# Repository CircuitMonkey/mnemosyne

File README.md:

# mnemosyne
Flash based NES Cartridge and programmer. Experimental project.

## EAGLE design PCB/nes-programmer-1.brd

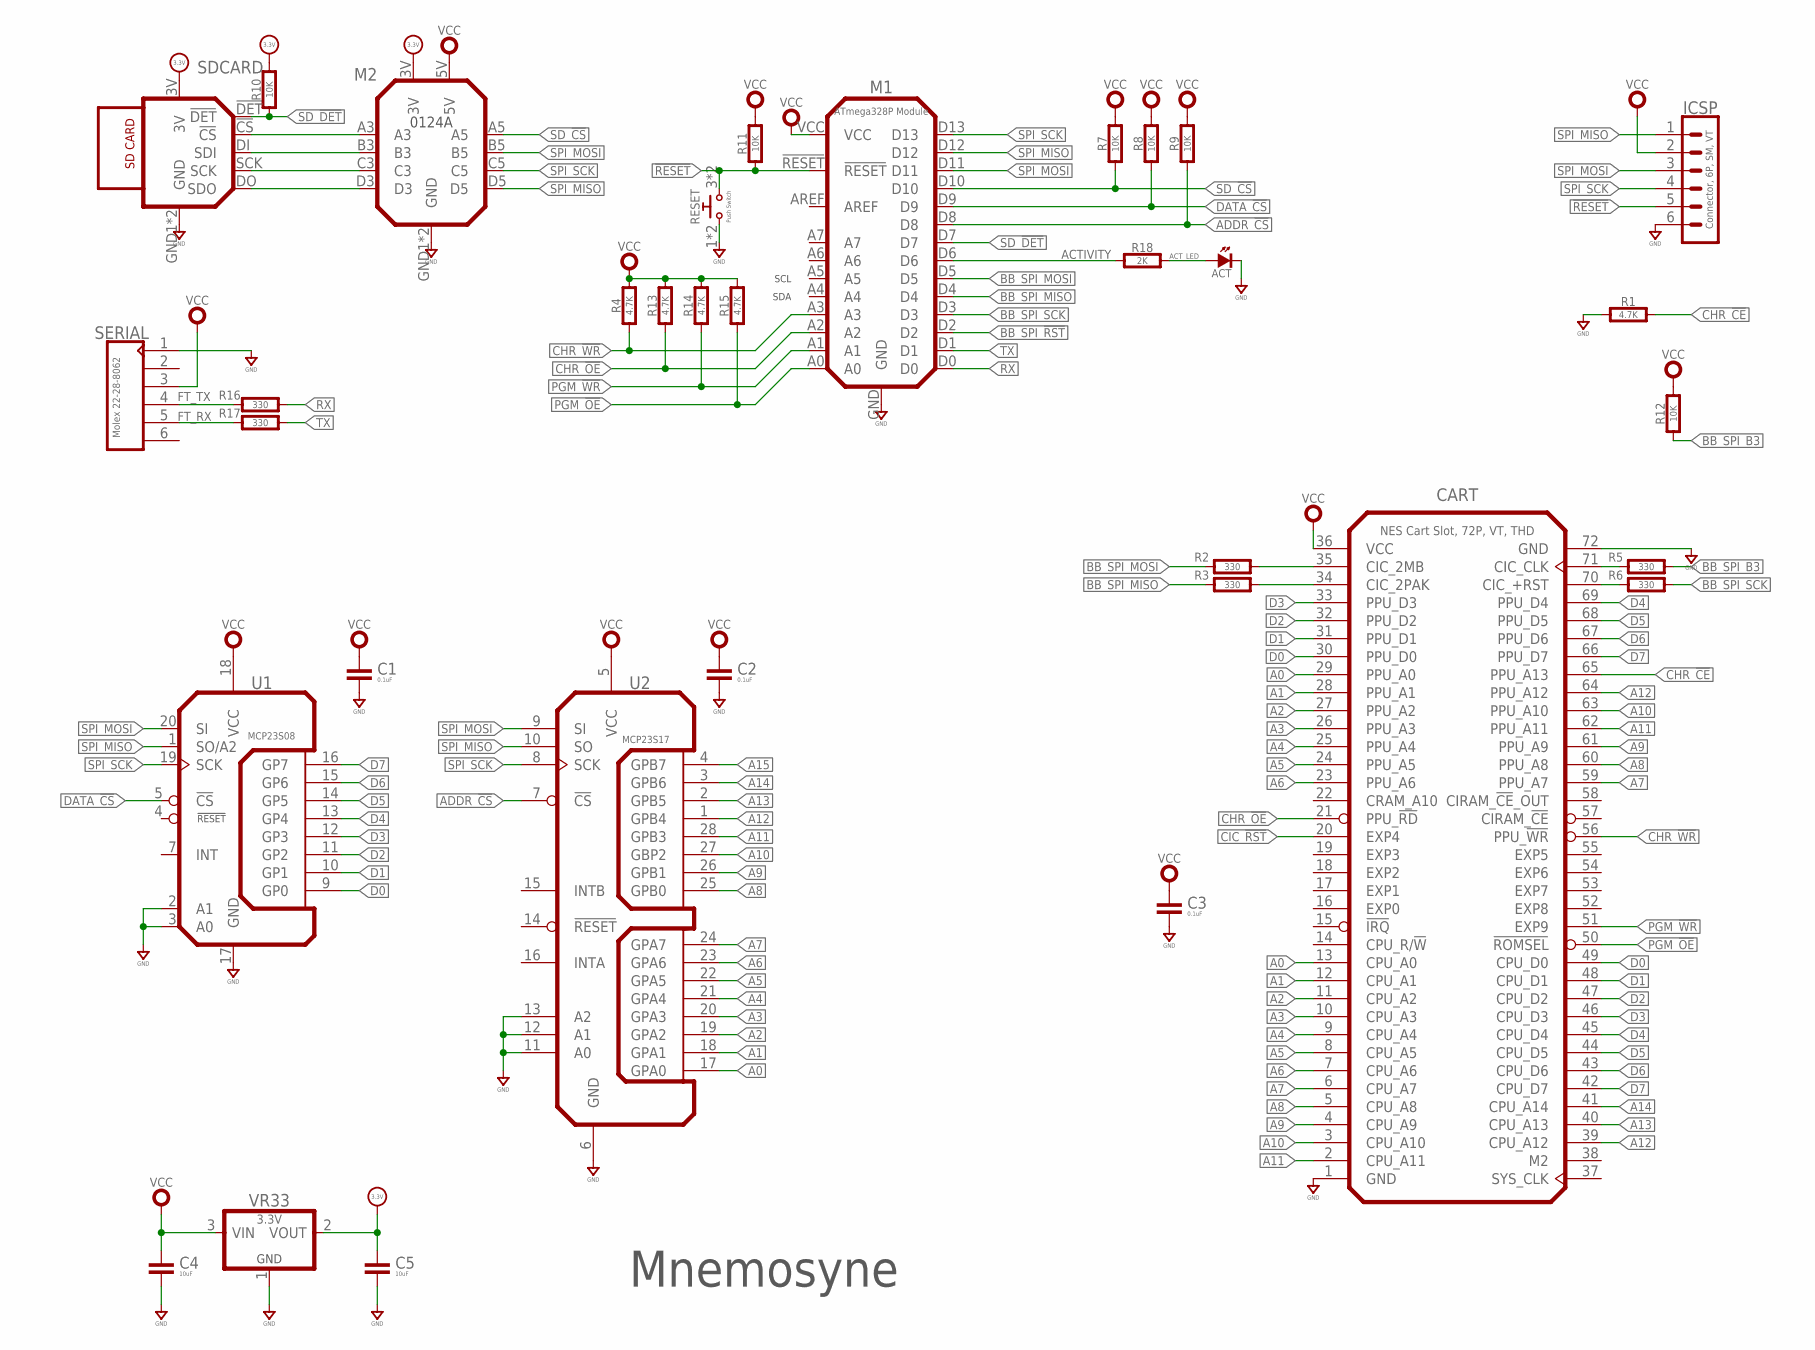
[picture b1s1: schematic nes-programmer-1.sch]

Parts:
ACT: SMT0603; SMD_0603
C1, C2, C3: 0.1uF; 0603-CAP
C4, C5: 10uF; 0603-CAP
CART: NES Cart Slot, 72P, VT, THD; NES-CONNECTOR-VT-THD
ICSP: Connector, 6P, SM, VT; BM06B-SRSS-TB
M1: ATmega328P Module; 0119A
M2: 0124A
R1, R4, R13, R14, R15: 4.7K; 0603-RES
R2, R3, R5, R6, R16, R17: 330; 0603-RES
R7, R8, R9, R10, R11, R12: 10K; 0603-RES
R18: 2K; 0603-RES
RESET: Push Switch; B3SN
SDCARD: 0127REV-A; 0127A
SERIAL: Molex 22-28-8062; MA06X1-RA-THD
U1: MCP23S08; QFN-20
U2: MCP23S17; QFN-28-6X6
VR33: 3.3V; SOT-23

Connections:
!RESET: ICSP.5, M1.!RESET, R11.1, RESET.3 (2), RESET.4 (2)
+3.3V: C5.1, M2.3V, R10.2, SDCARD.3V, VR33.2 (VOUT)
A0: CART.13 (CPU_A0), CART.29 (PPU_A0), U2.17 (GPA0)
A1: CART.12 (CPU_A1), CART.28 (PPU_A1), U2.18 (GPA1)
A2: CART.11 (CPU_A2), CART.27 (PPU_A2), U2.19 (GPA2)
A3: CART.10 (CPU_A3), CART.26 (PPU_A3), U2.20 (GPA3)
A4: CART.9 (CPU_A4), CART.25 (PPU_A4), U2.21 (GPA4)
A5: CART.8 (CPU_A5), CART.24 (PPU_A5), U2.22 (GPA5)
A6: CART.7 (CPU_A6), CART.23 (PPU_A6), U2.23 (GPA6)
A7: CART.6 (CPU_A7), CART.59 (PPU_A7), U2.24 (GPA7)
A8: CART.5 (CPU_A8), CART.60 (PPU_A8), U2.25 (GPB0)
A9: CART.4 (CPU_A9), CART.61 (PPU_A9), U2.26 (GPB1)
A10: CART.3 (CPU_A10), CART.63 (PPU_A10), U2.27 (GBP2)
A11: CART.2 (CPU_A11), CART.62 (PPU_A11), U2.28 (GPB3)
A12: CART.39 (CPU_A12), CART.64 (PPU_A12), U2.1 (GPB4)
A13: CART.40 (CPU_A13), U2.2 (GPB5)
A14: CART.41 (CPU_A14), U2.3 (GPB6)
A15: U2.4 (GPB7)
ACTIVITY: M1.D6, R18.1
ACT_LED: ACT.A, R18.2
ADDR_!CS: M1.D8, R9.1, U2.7 (!CS)
BB_SPI_!RST: M1.D2
BB_SPI_B3: R5.2, R12.1
BB_SPI_MISO: M1.D4, R3.1
BB_SPI_MOSI: M1.D5, R2.1
BB_SPI_SCK: M1.D3, R6.2
CHR_!CE: CART.65 (PPU_A13), R1.2
CHR_!OE: CART.21 (PPU_!RD), M1.A2, R13.1
CHR_!WR: CART.56 (PPU_!WR), M1.A3, R4.1
CIC_2MB: CART.35 (CIC_2MB), R2.2
CIC_2PAK: CART.34 (CIC_2PAK), R3.2
CIC_!RST: CART.20 (EXP4)
CIC_+RST: CART.70 (CIC_+RST), R6.1
CIC_CLK: CART.71 (CIC_CLK), R5.1
D0: CART.30 (PPU_D0), CART.49 (CPU_D0), U1.9 (GP0)
D1: CART.31 (PPU_D1), CART.48 (CPU_D1), U1.10 (GP1)
D2: CART.32 (PPU_D2), CART.47 (CPU_D2), U1.11 (GP2)
D3: CART.33 (PPU_D3), CART.46 (CPU_D3), U1.12 (GP3)
D4: CART.45 (CPU_D4), CART.69 (PPU_D4), U1.13 (GP4)
D5: CART.44 (CPU_D5), CART.68 (PPU_D5), U1.14 (GP5)
D6: CART.43 (CPU_D6), CART.67 (PPU_D6), U1.15 (GP6)
D7: CART.42 (CPU_D7), CART.66 (PPU_D7), U1.16 (GP7)
DATA_!CS: M1.D9, R8.1, U1.5 (!CS)
FT_RX: R17.1, SERIAL.5
FT_TX: R16.1, SERIAL.4
GND: ACT.K (C), C1.2, C2.2, C3.2, C4.2, C5.2, CART.1 (GND), CART.72 (GND), ICSP.6, M1.GND, M2.GND1 (GND), M2.GND2 (GND), R1.1, RESET.1, RESET.2 (1), SDCARD.GND1 (GND), SDCARD.GND2 (GND), SERIAL.1, U1.2 (A1), U1.3 (A0), U1.17 (GND), U2.6 (GND), U2.11 (A0), U2.12 (A1), U2.13 (A2), VR33.1 (GND)
unnamed: M2.D3, SDCARD.DO (SDO)
unnamed: M2.C3, SDCARD.SCK
unnamed: M2.B3, SDCARD.DI (SDI)
unnamed: M2.A3, SDCARD.!CS
PGM_!OE: CART.50 (!ROMSEL), M1.A0, R15.1
PGM_!WR: CART.51 (EXP9), M1.A1, R14.1
RX: M1.D0, R16.2
SD_!CS: M1.D10, M2.A5, R7.1
SD_!DET: M1.D7, R10.1, SDCARD.!DET
SPI_MISO: ICSP.1, M1.D12, M2.D5, U1.1 (SO/A2), U2.10 (SO)
SPI_MOSI: ICSP.3, M1.D11, M2.B5, U1.20 (SI), U2.9 (SI)
SPI_SCK: ICSP.4, M1.D13, M2.C5, U1.19 (SCK), U2.8 (SCK)
TX: M1.D1, R17.2
VCC: C1.1, C2.1, C3.1, C4.1, CART.36 (VCC), ICSP.2, M1.VCC, M2.5V, R4.2, R7.2, R8.2, R9.2, R11.2, R12.2, R13.2, R14.2, R15.2, SERIAL.3, U1.18 (VCC), U2.5 (VCC), VR33.3 (VIN)

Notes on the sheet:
SDA
SCL
Mnemosyne

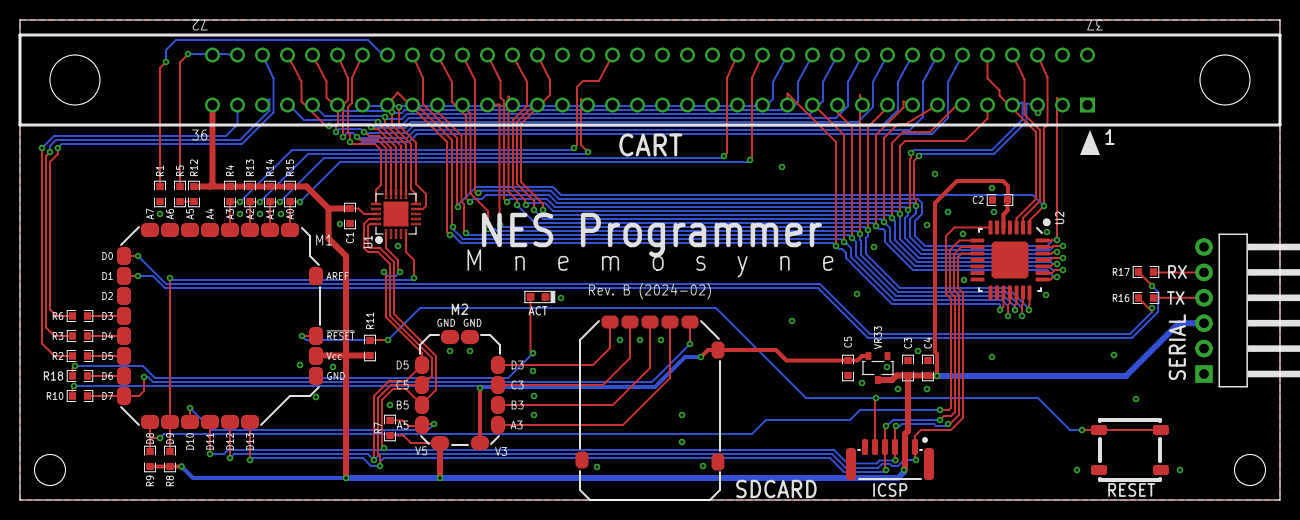
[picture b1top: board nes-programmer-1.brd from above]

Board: 2 copper layers, 126.0 x 48.0 mm, 34 parts (0 on the bottom side), 57 nets.

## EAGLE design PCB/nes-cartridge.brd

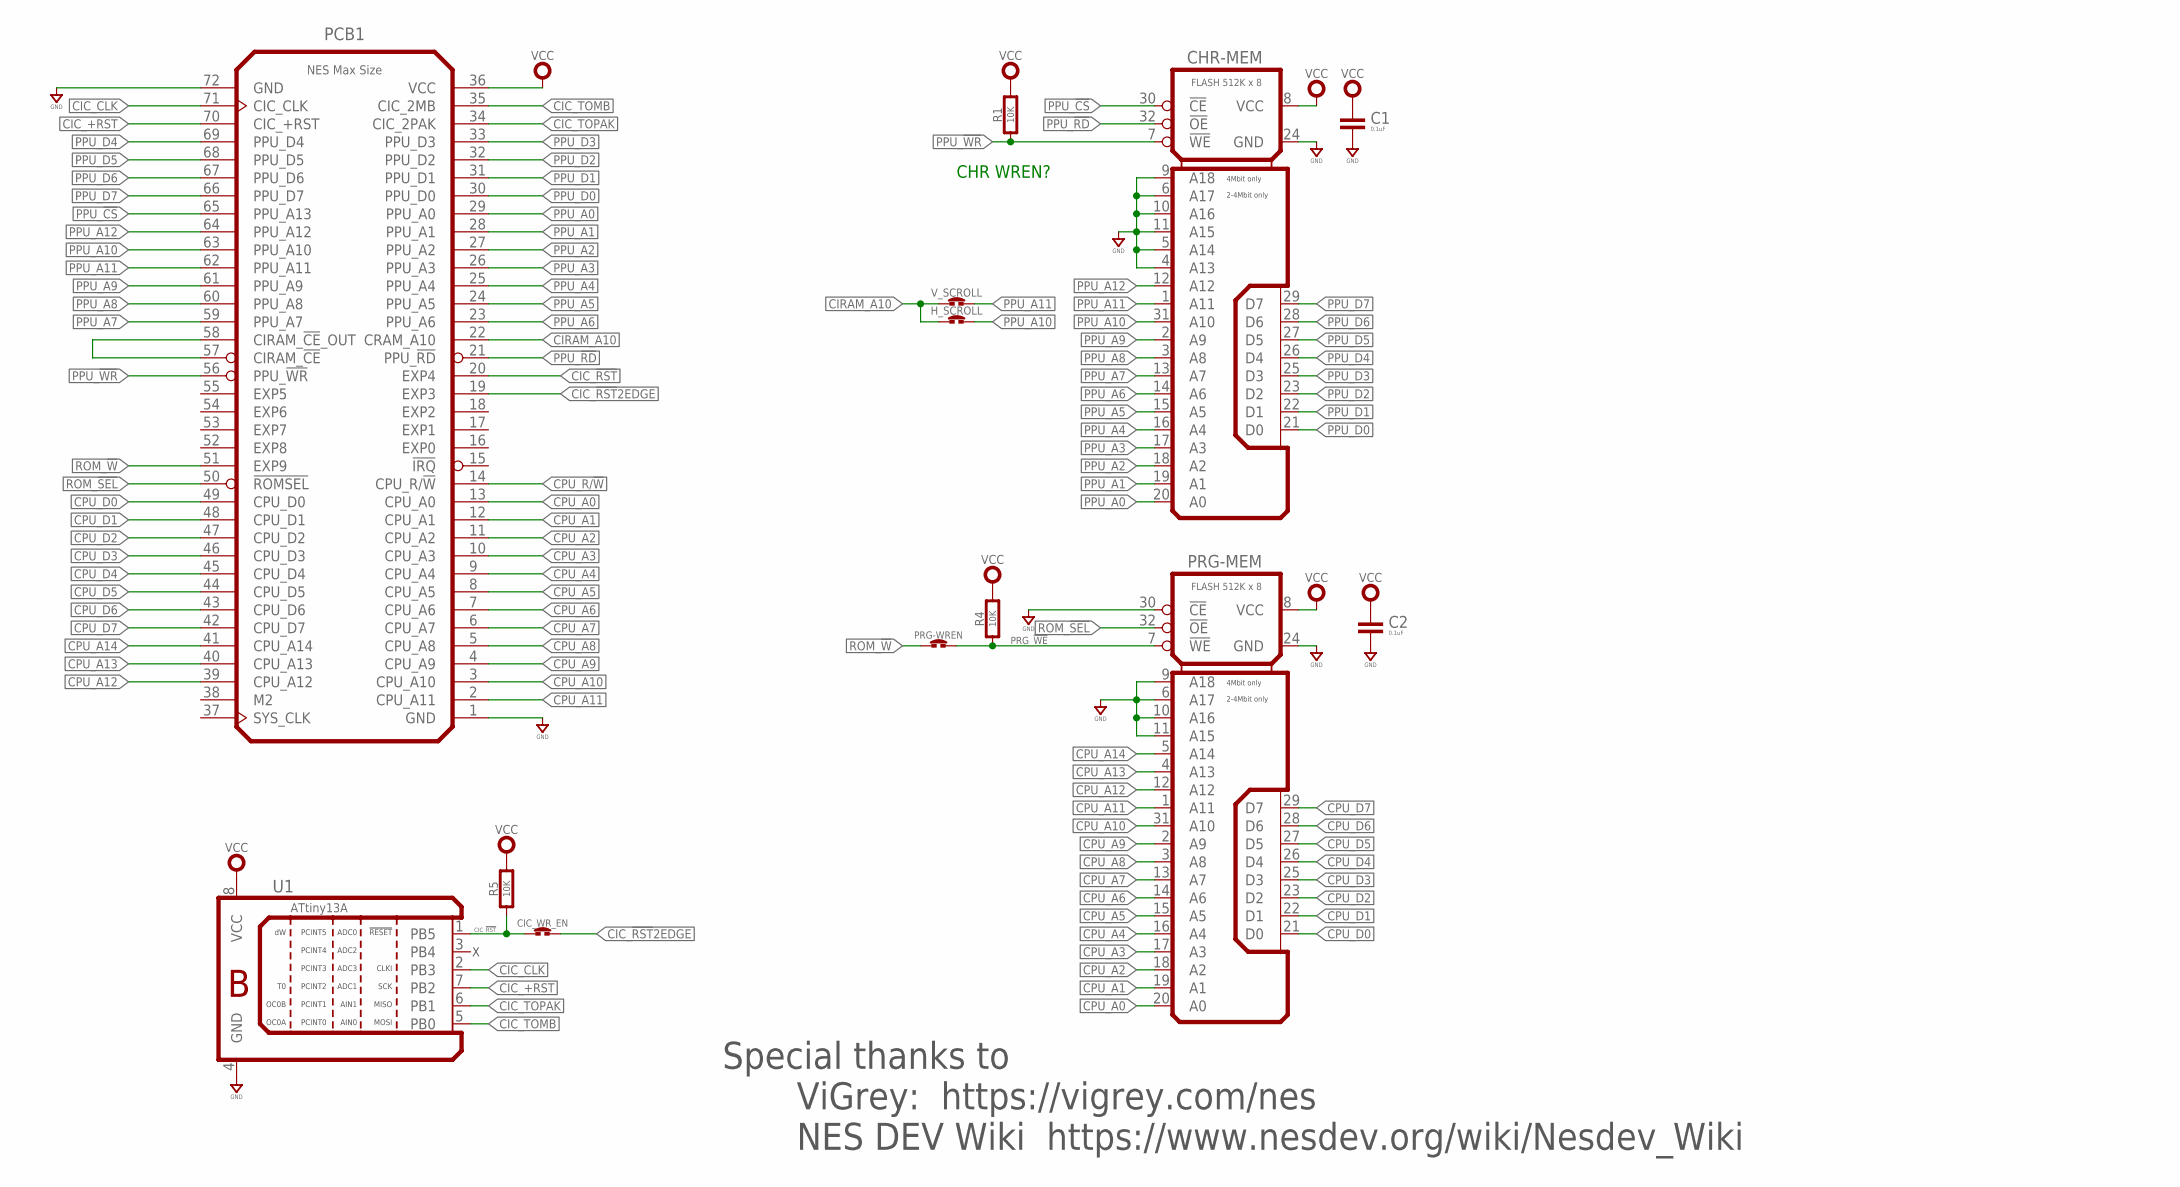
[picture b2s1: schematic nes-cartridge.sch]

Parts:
C1, C2: 0.1uF; 0603-CAP
CHR-MEM: FLASH 512K x 8; TSOP32-14X8MM
CIC_WR_EN: SOLDER_JUMPER-80MIL-RND; SOLDER_JUMP_80MIL_RND
H_SCROLL: SOLDER_JUMPER-80MIL-RND; SOLDER_JUMP_80MIL_RND
PCB1: NES Max Size; NES-1-MIN
PRG-MEM: FLASH 512K x 8; TSOP32-14X8MM
PRG-WREN: SOLDER_JUMPER-80MIL-RND; SOLDER_JUMP_80MIL_RND
R1, R4, R5: 10K; 0603-RES
U1: ATtiny13A; SOIC-8S2
V_SCROLL: SOLDER_JUMPER-80MIL-RND; SOLDER_JUMP_80MIL_RND

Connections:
CIC_!RST: CIC_WR_EN.1, PCB1.20 (EXP4), R5.1, U1.1 (PB5)
CIC_!RST!2EDGE: CIC_WR_EN.2, PCB1.19 (EXP3)
CIC_+RST: PCB1.70 (CIC_+RST), U1.7 (PB2)
CIC_CLK: PCB1.71 (CIC_CLK), U1.2 (PB3)
CIC_TOMB: PCB1.35 (CIC_2MB), U1.5 (PB0)
CIC_TOPAK: PCB1.34 (CIC_2PAK), U1.6 (PB1)
CIRAM_A10: H_SCROLL.1, PCB1.22 (CRAM_A10), V_SCROLL.1
CPU_A0: PCB1.13 (CPU_A0), PRG-MEM.20 (A0)
CPU_A1: PCB1.12 (CPU_A1), PRG-MEM.19 (A1)
CPU_A2: PCB1.11 (CPU_A2), PRG-MEM.18 (A2)
CPU_A3: PCB1.10 (CPU_A3), PRG-MEM.17 (A3)
CPU_A4: PCB1.9 (CPU_A4), PRG-MEM.16 (A4)
CPU_A5: PCB1.8 (CPU_A5), PRG-MEM.15 (A5)
CPU_A6: PCB1.7 (CPU_A6), PRG-MEM.14 (A6)
CPU_A7: PCB1.6 (CPU_A7), PRG-MEM.13 (A7)
CPU_A8: PCB1.5 (CPU_A8), PRG-MEM.3 (A8)
CPU_A9: PCB1.4 (CPU_A9), PRG-MEM.2 (A9)
CPU_A10: PCB1.3 (CPU_A10), PRG-MEM.31 (A10)
CPU_A11: PCB1.2 (CPU_A11), PRG-MEM.1 (A11)
CPU_A12: PCB1.39 (CPU_A12), PRG-MEM.12 (A12)
CPU_A13: PCB1.40 (CPU_A13), PRG-MEM.4 (A13)
CPU_A14: PCB1.41 (CPU_A14), PRG-MEM.5 (A14)
CPU_D0: PCB1.49 (CPU_D0), PRG-MEM.21 (D0)
CPU_D1: PCB1.48 (CPU_D1), PRG-MEM.22 (D1)
CPU_D2: PCB1.47 (CPU_D2), PRG-MEM.23 (D2)
CPU_D3: PCB1.46 (CPU_D3), PRG-MEM.25 (D3)
CPU_D4: PCB1.45 (CPU_D4), PRG-MEM.26 (D4)
CPU_D5: PCB1.44 (CPU_D5), PRG-MEM.27 (D5)
CPU_D6: PCB1.43 (CPU_D6), PRG-MEM.28 (D6)
CPU_D7: PCB1.42 (CPU_D7), PRG-MEM.29 (D7)
CPU_R/!W: PCB1.14 (CPU_R/!W)
GND: C1.2, C2.2, CHR-MEM.4 (A13), CHR-MEM.5 (A14), CHR-MEM.6 (A17), CHR-MEM.9 (A18), CHR-MEM.10 (A16), CHR-MEM.11 (A15), CHR-MEM.24 (GND), PCB1.1 (GND), PCB1.72 (GND), PRG-MEM.6 (A17), PRG-MEM.9 (A18), PRG-MEM.10 (A16), PRG-MEM.11 (A15), PRG-MEM.24 (GND), U1.4 (GND)
unnamed: PCB1.57 (CIRAM_!CE), PCB1.58 (CIRAM_!CE!_OUT)
PPU_!CS: CHR-MEM.30 (!CE), PCB1.65 (PPU_A13)
PPU_!RD: CHR-MEM.32 (!OE), PCB1.21 (PPU_!RD)
PPU_!WR: CHR-MEM.7 (!WE), PCB1.56 (PPU_!WR), R1.1
PPU_A0: CHR-MEM.20 (A0), PCB1.29 (PPU_A0)
PPU_A1: CHR-MEM.19 (A1), PCB1.28 (PPU_A1)
PPU_A2: CHR-MEM.18 (A2), PCB1.27 (PPU_A2)
PPU_A3: CHR-MEM.17 (A3), PCB1.26 (PPU_A3)
PPU_A4: CHR-MEM.16 (A4), PCB1.25 (PPU_A4)
PPU_A5: CHR-MEM.15 (A5), PCB1.24 (PPU_A5)
PPU_A6: CHR-MEM.14 (A6), PCB1.23 (PPU_A6)
PPU_A7: CHR-MEM.13 (A7), PCB1.59 (PPU_A7)
PPU_A8: CHR-MEM.3 (A8), PCB1.60 (PPU_A8)
PPU_A9: CHR-MEM.2 (A9), PCB1.61 (PPU_A9)
PPU_A10: CHR-MEM.31 (A10), H_SCROLL.2, PCB1.63 (PPU_A10)
PPU_A11: CHR-MEM.1 (A11), PCB1.62 (PPU_A11), V_SCROLL.2
PPU_A12: CHR-MEM.12 (A12), PCB1.64 (PPU_A12)
PPU_D0: CHR-MEM.21 (D0), PCB1.30 (PPU_D0)
PPU_D1: CHR-MEM.22 (D1), PCB1.31 (PPU_D1)
PPU_D2: CHR-MEM.23 (D2), PCB1.32 (PPU_D2)
PPU_D3: CHR-MEM.25 (D3), PCB1.33 (PPU_D3)
PPU_D4: CHR-MEM.26 (D4), PCB1.69 (PPU_D4)
PPU_D5: CHR-MEM.27 (D5), PCB1.68 (PPU_D5)
PPU_D6: CHR-MEM.28 (D6), PCB1.67 (PPU_D6)
PPU_D7: CHR-MEM.29 (D7), PCB1.66 (PPU_D7)
PRG_!WE: PRG-MEM.7 (!WE), PRG-WREN.2, R4.1
ROM_!SEL: PCB1.50 (!ROMSEL), PRG-MEM.32 (!OE)
ROM_!W: PCB1.51 (EXP9), PRG-WREN.1
VCC: C1.1, C2.1, CHR-MEM.8 (VCC), PCB1.36 (VCC), PRG-MEM.8 (VCC), R1.2, R4.2, R5.2, U1.8 (VCC)

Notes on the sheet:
Special thanks to ViGrey: https://vigrey.com/nes NES DEV Wiki https://www.nesdev.org/wiki/Nesdev_Wiki
CHR WREN?

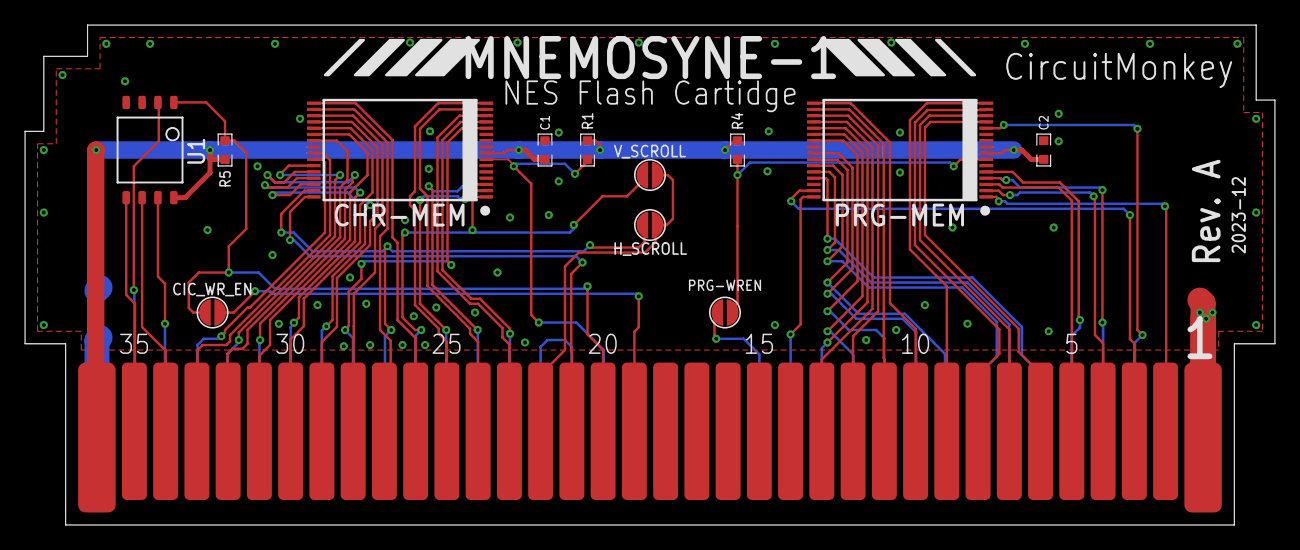
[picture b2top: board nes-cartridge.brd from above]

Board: 2 copper layers, 100.0 x 40.0 mm, 13 parts (0 on the bottom side), 60 nets.

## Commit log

2023-12-02 First upload
2023-12-06 Cart board and programmer board checkpoint.
2023-12-23 Final tweaks.
2023-12-23 PCBs as FABed in 12-2023
2024-01-12 Added Cap values, bump rev due to PCB change.
2024-01-12 Bump rev to B. Fix connector hole spacing issue.
2024-01-12 Creat BOMs
